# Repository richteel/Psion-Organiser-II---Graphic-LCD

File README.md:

# Psion Organiser II - Graphic-LCD
Replacing internals of a Psion Organiser II to include a Graphic LCD

- MCP23017 & MCP23S17 Product Pages
 - <a href="https://www.microchip.com/wwwproducts/en/mcp23017">Microchip MCP23017</a>
 - <a href="https://www.microchip.com/wwwproducts/en/mcp23S17">Microchip MCP23S17</a>
 - <a href="https://www.adafruit.com/product/732">Adafruit MCP23017</a>
- MCP23017 & MCP23S17 Datasheets
 - <a href="https://ww1.microchip.com/downloads/en/DeviceDoc/20001952C.pdf">Microchip (2016)</a>
 - <a href="https://cdn-shop.adafruit.com/datasheets/mcp23017.pdf">Adafruit (Microchip 2007)</a>

There is not much here for this project and it has been a while since I worked on the project. I don't know when I will get back to it. I did see a really cool project today along these same lines using an OLED display. The project is on YouTube by user <a href="https://www.youtube.com/channel/UCNweFQHar6-JMdXFk-MrOtQ/videos">A Menadue</a>.

I may abandon this project and try to do what A Menadue is doing as he has been able to do a great deal more work on this and in my opinion done a far better job that I would. I have been debating on attempting to recreate what Psion did or doing something different to take advantage of additional I/O and the graphics display.

The first video of A Menadue's project is at <a href="https://youtu.be/v2YWStDrQIs">https://youtu.be/v2YWStDrQIs</a>.

<a href="https://richteel.github.io/Psion-Organiser-II---Graphic-LCD/">GitHub Pages</a> - Currently blank.

The display that I've used is a Crystalfontz LCD <a href="https://www.crystalfontz.com/product/cfag12232dyyhva-transflective-graphic-lcd-122x32">CFAG12232D-YYH-VA</a>. I also used an Arduino Micro for the microcontroller to run the code. I was planning on using a Raspberry Pi Zero W but with Raspberry Pi Pico/RP2040 and an ESP32 seem link a better option.

Here are some photos taken of the sample code running the display.

<a href="https://github.com/richteel/Psion-Organiser-II---Graphic-LCD/blob/main/Code/sketch_April_Fools/Facebook/Psion%20April%20Fools.mp4?raw=true">Video of source code running</a>

<video width="320" height="240" controls>
  <source src="https://github.com/richteel/Psion-Organiser-II---Graphic-LCD/blob/main/Code/sketch_April_Fools/Facebook/Psion%20April%20Fools.mp4?raw=true" type="video/mp4">
Your browser does not support the video tag.
</video>

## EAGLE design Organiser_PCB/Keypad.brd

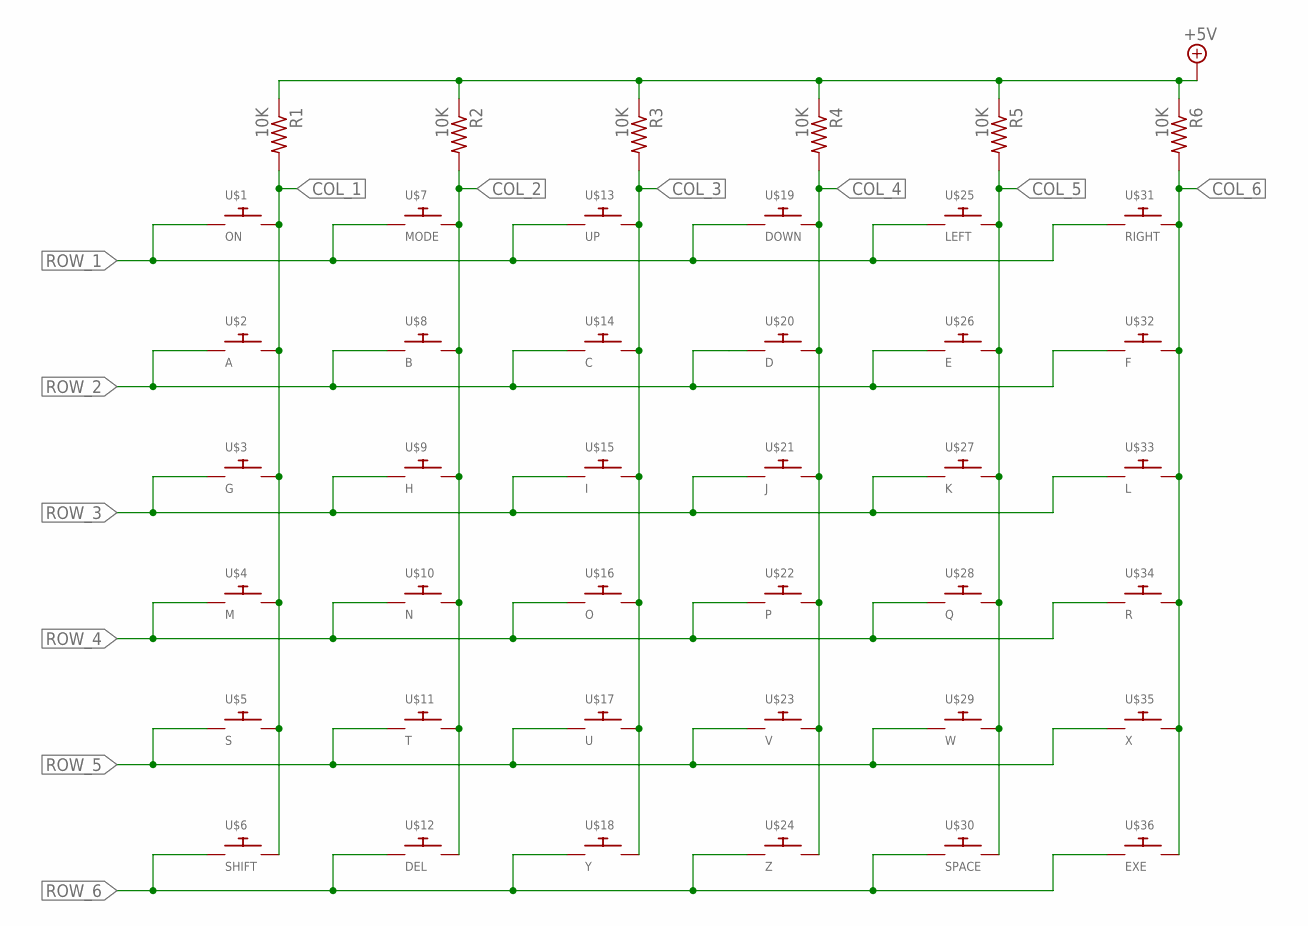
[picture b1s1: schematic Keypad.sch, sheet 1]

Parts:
R1, R2, R3, R4, R5, R6: 10K; M0805
U$1: ON; KEYPAD_RND
U$2: A; KEYPAD_RND
U$3: G; KEYPAD_RND
U$4: M; KEYPAD_RND
U$5: S; KEYPAD_RND
U$6: SHIFT; KEYPAD_RND
U$7: MODE; KEYPAD_RND
U$8: B; KEYPAD_RND
U$9: H; KEYPAD_RND
U$10: N; KEYPAD_RND
U$11: T; KEYPAD_RND
U$12: DEL; KEYPAD_RND
U$13: UP; KEYPAD_RND
U$14: C; KEYPAD_RND
U$15: I; KEYPAD_RND
U$16: O; KEYPAD_RND
U$17: U; KEYPAD_RND
U$18: Y; KEYPAD_RND
U$19: DOWN; KEYPAD_RND
U$20: D; KEYPAD_RND
U$21: J; KEYPAD_RND
U$22: P; KEYPAD_RND
U$23: V; KEYPAD_RND
U$24: Z; KEYPAD_RND
U$25: LEFT; KEYPAD_RND
U$26: E; KEYPAD_RND
U$27: K; KEYPAD_RND
U$28: Q; KEYPAD_RND
U$29: W; KEYPAD_RND
U$30: SPACE; KEYPAD_RND
U$31: RIGHT; KEYPAD_RND
U$32: F; KEYPAD_RND
U$33: L; KEYPAD_RND
U$34: R; KEYPAD_RND
U$35: X; KEYPAD_RND
U$36: EXE; KEYPAD_RND
U$40: TEELSYS_LOGO_ART_2BOTTOM; TEELSYS_LOGO_ART_BOTTOM_2

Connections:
+5V: R1.1, R2.1, R3.1, R4.1, R5.1, R6.1; also elsewhere on the board
COL_1: R1.2, U$1.P$2, U$2.P$2, U$3.P$2, U$4.P$2, U$5.P$2, U$6.P$2; also elsewhere on the board
COL_2: R2.2, U$7.P$2, U$8.P$2, U$9.P$2, U$10.P$2, U$11.P$2, U$12.P$2; also elsewhere on the board
COL_3: R3.2, U$13.P$2, U$14.P$2, U$15.P$2, U$16.P$2, U$17.P$2, U$18.P$2; also elsewhere on the board
COL_4: R4.2, U$19.P$2, U$20.P$2, U$21.P$2, U$22.P$2, U$23.P$2, U$24.P$2; also elsewhere on the board
COL_5: R5.2, U$25.P$2, U$26.P$2, U$27.P$2, U$28.P$2, U$29.P$2, U$30.P$2; also elsewhere on the board
COL_6: R6.2, U$31.P$2, U$32.P$2, U$33.P$2, U$34.P$2, U$35.P$2, U$36.P$2; also elsewhere on the board
ROW_1: U$1.P$1, U$7.P$1, U$13.P$1, U$19.P$1, U$25.P$1, U$31.P$1; also elsewhere on the board
ROW_2: U$2.P$1, U$8.P$1, U$14.P$1, U$20.P$1, U$26.P$1, U$32.P$1; also elsewhere on the board
ROW_3: U$3.P$1, U$9.P$1, U$15.P$1, U$21.P$1, U$27.P$1, U$33.P$1; also elsewhere on the board
ROW_4: U$4.P$1, U$10.P$1, U$16.P$1, U$22.P$1, U$28.P$1, U$34.P$1; also elsewhere on the board
ROW_5: U$5.P$1, U$11.P$1, U$17.P$1, U$23.P$1, U$29.P$1, U$35.P$1; also elsewhere on the board
ROW_6: U$6.P$1, U$12.P$1, U$18.P$1, U$24.P$1, U$30.P$1, U$36.P$1; also elsewhere on the board

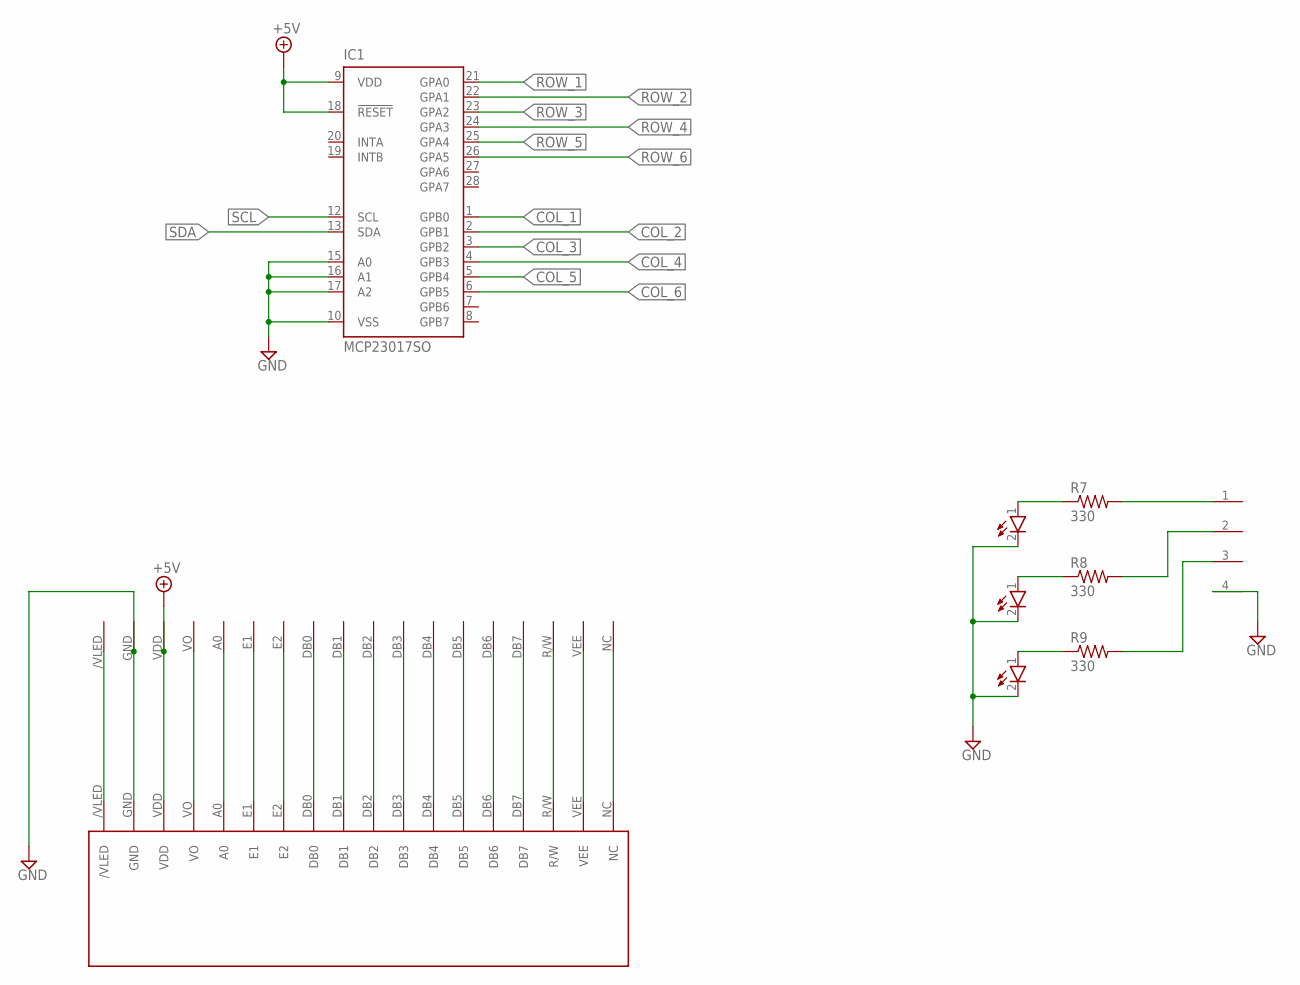
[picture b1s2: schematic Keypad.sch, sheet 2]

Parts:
IC1: MCP23017SO; SO28W
LED1: RED; HEADER-1X2
LED2: Green; HEADER-1X2
LED3: BLUE; HEADER-1X2
R7, R8, R9: 330; M0805
U$38: HEADER-1X18-LCD
U$39: HEADER-1X4
U$73: LCD_CFAL12832A022

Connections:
+5V: IC1.9 (VDD), IC1.18 (!RESET), U$38.VDD, U$73.VDD; also elsewhere on the board
/VLED: U$38./VLED, U$73./VLED
A0: U$38.A0, U$73.A0
COL_1: IC1.1 (GPB0); also elsewhere on the board
COL_2: IC1.2 (GPB1); also elsewhere on the board
COL_3: IC1.3 (GPB2); also elsewhere on the board
COL_4: IC1.4 (GPB3); also elsewhere on the board
COL_5: IC1.5 (GPB4); also elsewhere on the board
COL_6: IC1.6 (GPB5); also elsewhere on the board
DB0: U$38.DB0, U$73.DB0
DB1: U$38.DB1, U$73.DB1
DB2: U$38.DB2, U$73.DB2
DB3: U$38.DB3, U$73.DB3
DB4: U$38.DB4, U$73.DB4
DB5: U$38.DB5, U$73.DB5
DB6: U$38.DB6, U$73.DB6
DB7: U$38.DB7, U$73.DB7
E1: U$38.E1, U$73.E1
E2: U$38.E2, U$73.E2
GND: IC1.10 (VSS), IC1.15 (A0), IC1.16 (A1), IC1.17 (A2), LED1.2 (K), LED2.2 (K), LED3.2 (K), U$38.GND, U$39.4, U$73.GND
unnamed: LED3.1 (A), R9.1
unnamed: LED2.1 (A), R8.1
unnamed: LED1.1 (A), R7.1
unnamed: R9.2, U$39.3
unnamed: R8.2, U$39.2
unnamed: R7.2, U$39.1
NC: U$38.NC, U$73.NC
R/W: U$38.R/W, U$73.R/W
ROW_1: IC1.21 (GPA0); also elsewhere on the board
ROW_2: IC1.22 (GPA1); also elsewhere on the board
ROW_3: IC1.23 (GPA2); also elsewhere on the board
ROW_4: IC1.24 (GPA3); also elsewhere on the board
ROW_5: IC1.25 (GPA4); also elsewhere on the board
ROW_6: IC1.26 (GPA5); also elsewhere on the board
SCL: IC1.12 (SCL)
SDA: IC1.13 (SDA)
VEE: U$38.VEE, U$73.VEE
VO: U$38.VO, U$73.VO

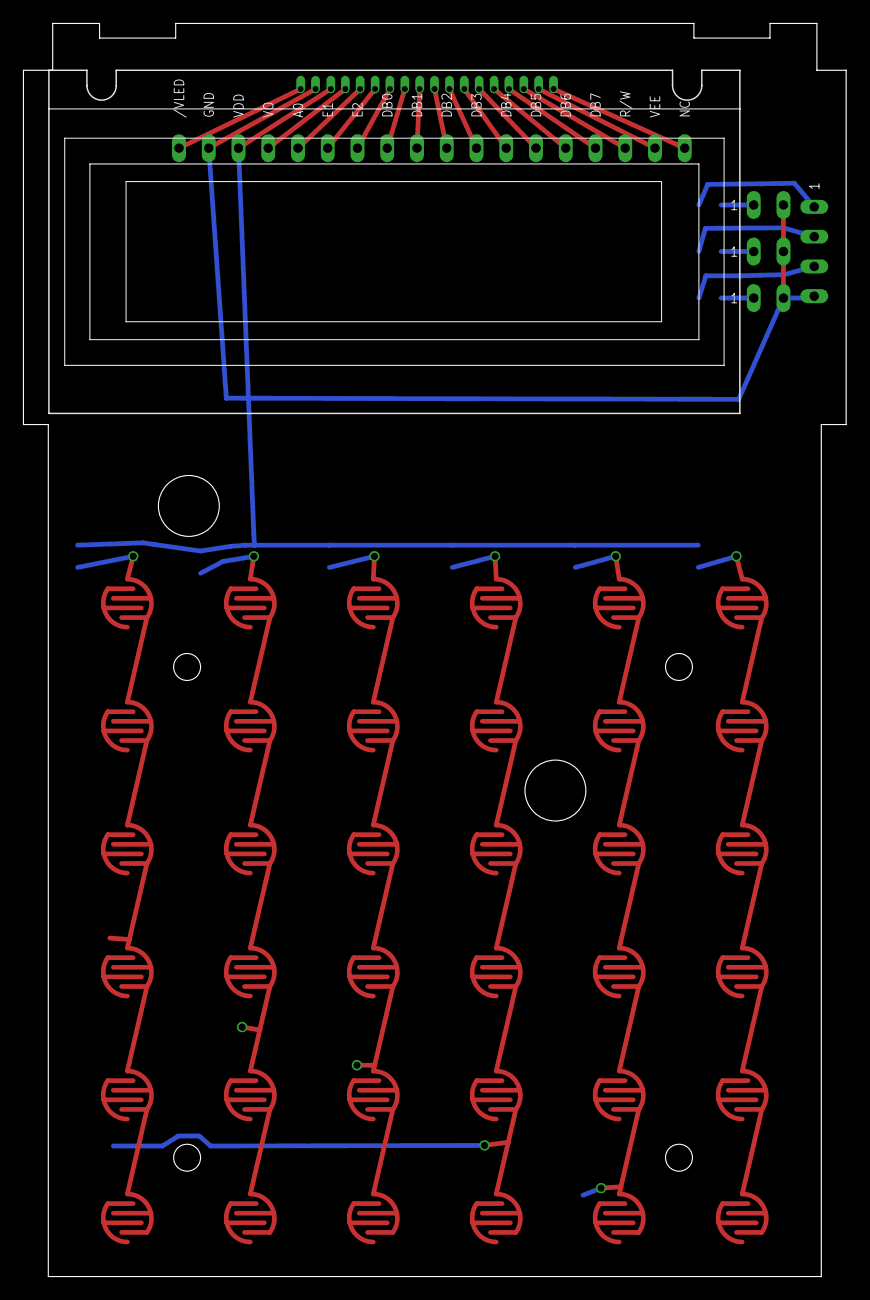
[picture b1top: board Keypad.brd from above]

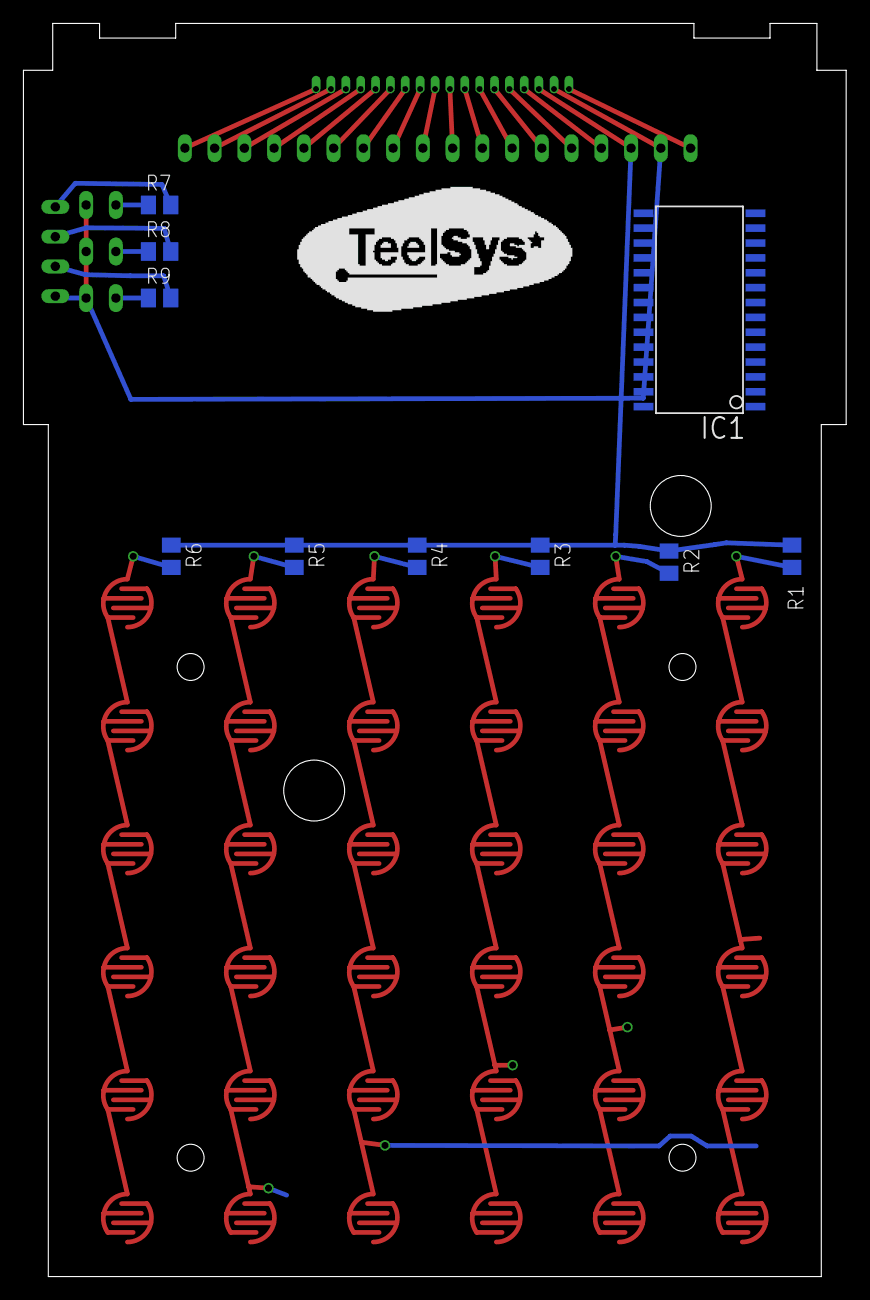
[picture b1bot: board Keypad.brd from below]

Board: 2 copper layers, 70.2 x 107.0 mm, 53 parts (10 on the bottom side), 36 nets.

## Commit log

2021-04-13 Initial PCB Design
2021-04-13 Modified git ignore to exclude Eagle backup files
2021-04-15 Create blank.yml
    Trying some build actions
2021-04-15 Rename blank.yml to githubci.yml
2021-04-15 Update README.md
    Test action
2021-04-16 Clean gh-pages branch
2021-04-16 Update githubci.yml
    Comment all
2021-04-16 Update githubci.yml
    cleared
2021-04-17 Adding Arduino code for the keyboard This code uses port operations on the MCP23017.
2021-04-18 Another keyboard test using the MCP23017 by pin rather than by port and including 3 LEDs
2021-04-20 Modified the code to work with the MCP23017 wired in straight rather than by port and added second MCP23017 for display. (Only backlight in use)
2021-04-20 Added graphics program that was used for April Fools joke on Facebook.
2021-04-20 Removed the photos folder as it was not necessary and consumed a lot of space.
2021-04-23 Added LED Shroud 3D Print files
2021-04-23 Adding initial code for LCD before making some change to the read/write control pins to speed up writing to the screen
2021-04-23 Modified code in an attempt to speed up the ClearScreen method.
    Setup takes 4,073 ms
2021-04-28 Moved hardware specific calls to separate class that inherits from the SED1520 class.
2021-04-29 Renamed SED1520_128x32_I2C to SED1520_122x32_I2C Added graphic functions
2021-05-08 Changed LCD to use MCP23S17 with SPI interface Reduced example execution time to draw on LCD from 4 seconds down to 251 ms (I2C to SPI)
2022-01-09 Just capturing changes that were made in the past in preparation with merging to main
2022-01-09 Updated README.md file
2022-01-09 Added link to video
